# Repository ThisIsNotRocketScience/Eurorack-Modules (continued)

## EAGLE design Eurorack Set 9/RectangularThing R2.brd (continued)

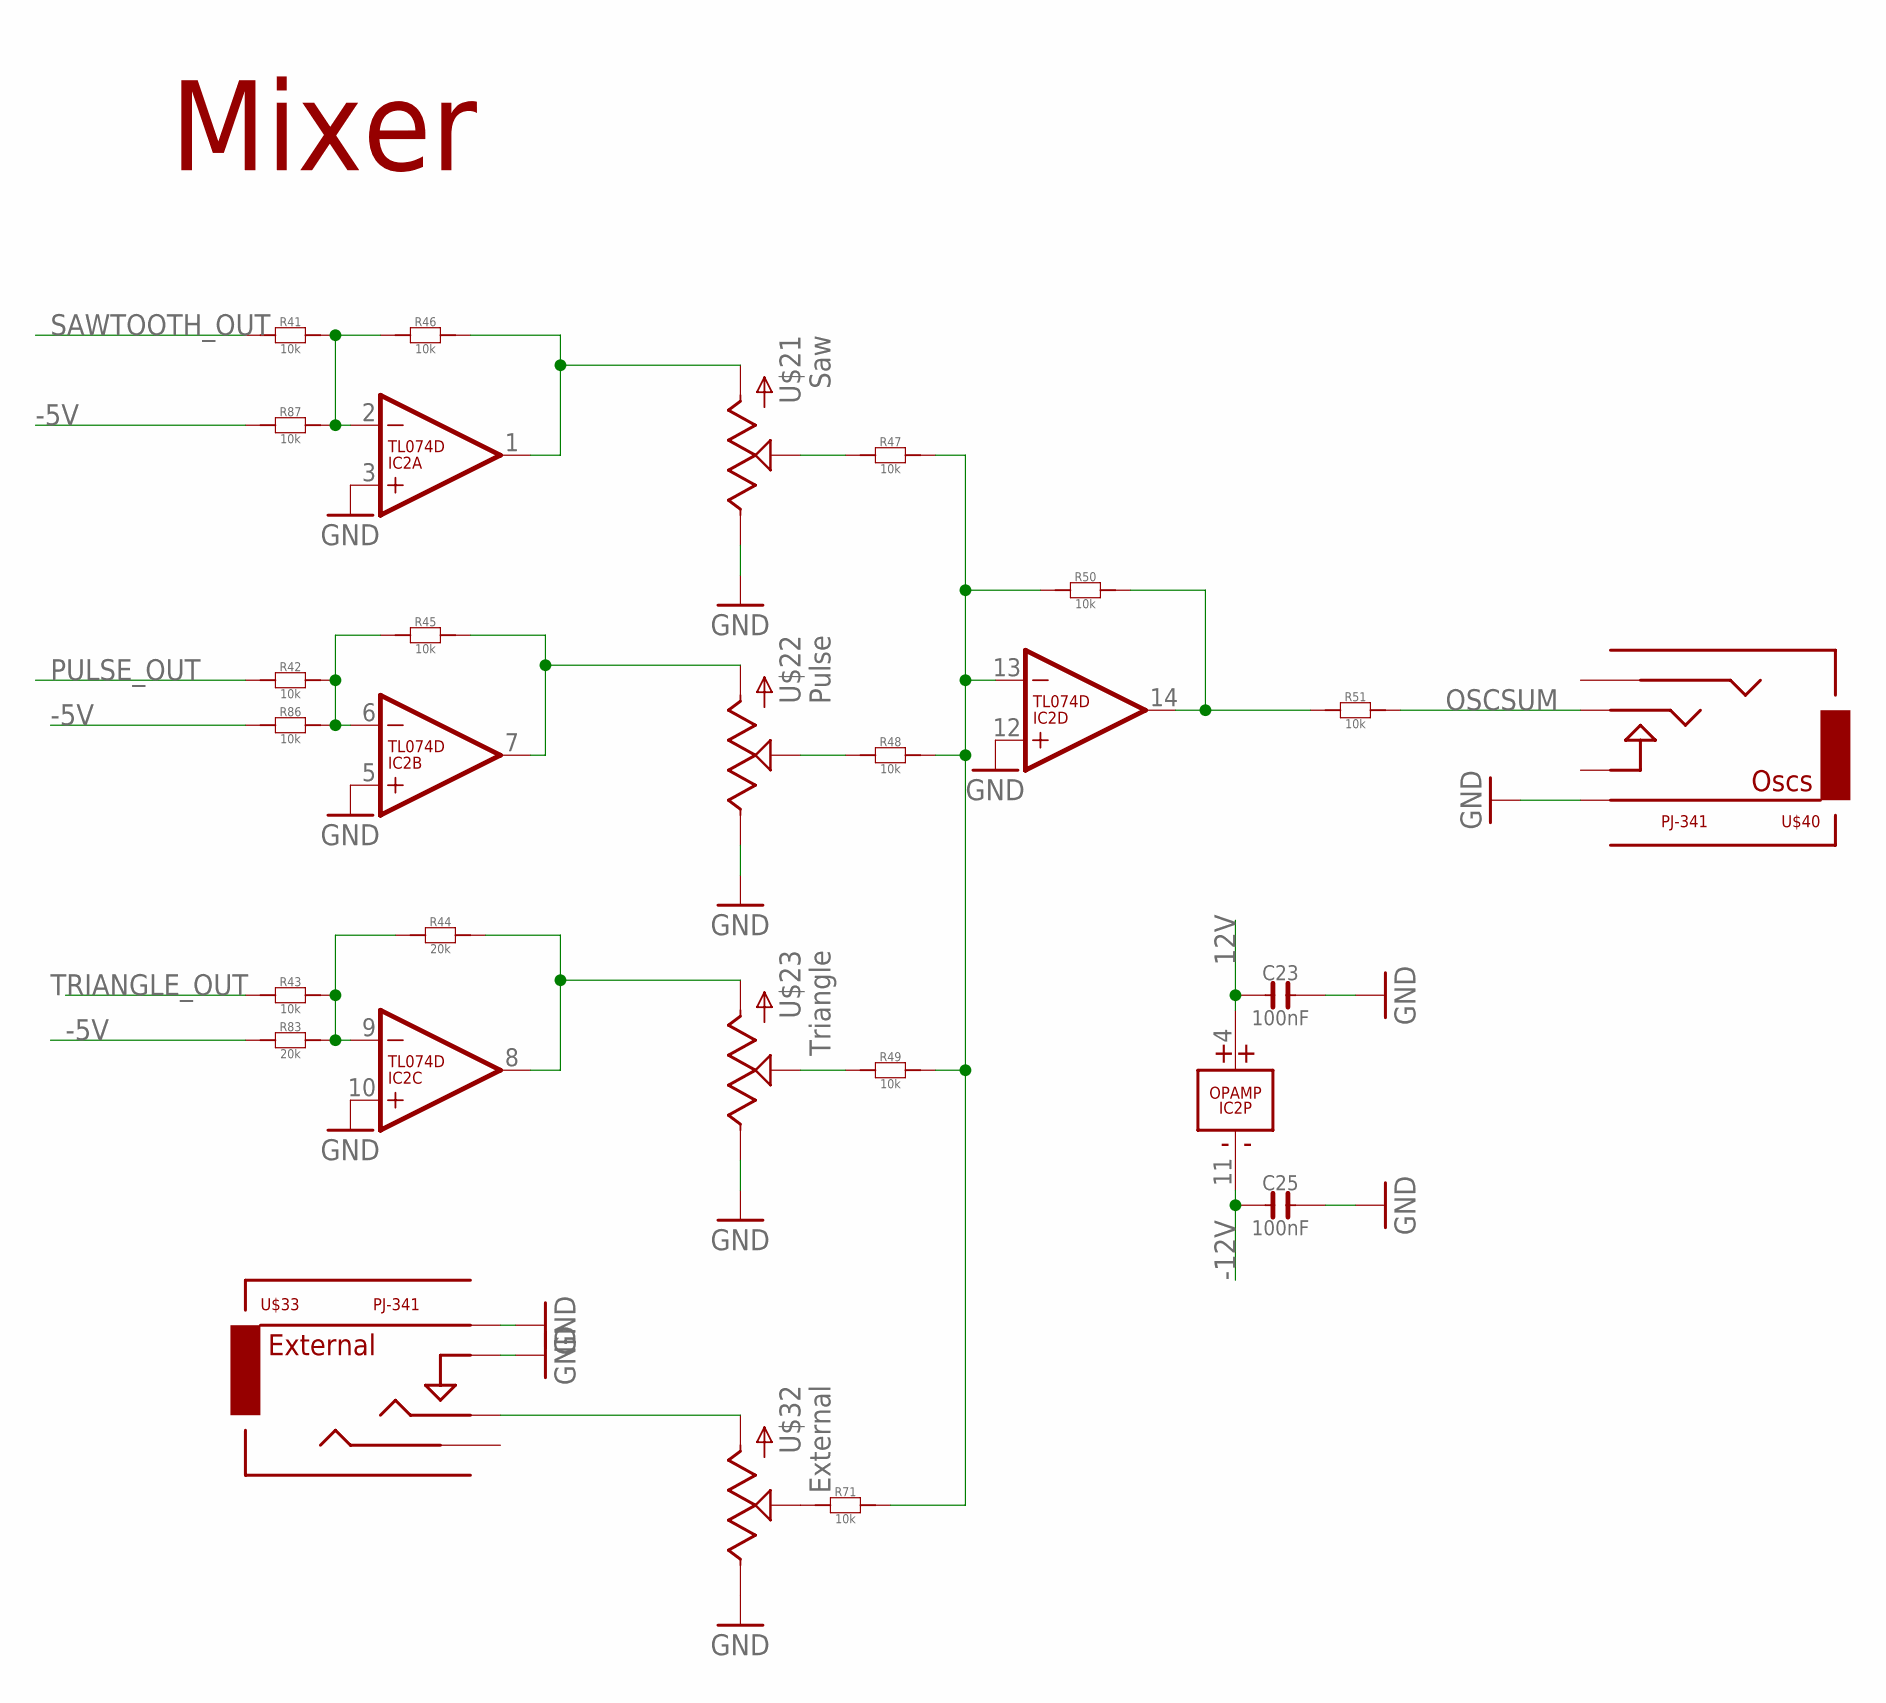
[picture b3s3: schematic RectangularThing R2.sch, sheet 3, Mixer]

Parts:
C23, C25: 100nF; C0603
IC2: TL074D; SO14
R41, R42, R43, R45, R46, R47, R48, R49, R50, R51, R71, R86, R87: 10k; R0603
R44, R83: 20k; R0603
U$21, U$22, U$23, U$32: POTZEPHPOT; OG-POTS_ALPS_POT_VERTICAL
U$33: PJ-341; 3.5MM-JACK-SWITCH-13MM-INPUT
U$40: PJ-341; 3.5MM-JACK-SWITCH-13MM-OUTPUT

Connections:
12V: C23.1, IC2.4 (V+); also elsewhere on the board
-5V: R83.1, R86.1, R87.1; also elsewhere on the board
-12V: C25.1, IC2.11 (V-); also elsewhere on the board
GND: C23.2, C25.2, IC2.3 (+IN), IC2.5 (+IN), IC2.10 (+IN), IC2.12 (+IN), U$21.P$1 (E), U$22.P$1 (E), U$23.P$1 (E), U$32.P$1 (E), U$33.RING@3 (RING), U$33.SWITCH@3 (SWITCH), U$40.RING@3 (RING); also elsewhere on the board
unnamed: IC2.14 (OUT), R50.2, R51.1
unnamed: IC2.13 (-IN), R47.2, R48.2, R49.2, R50.1, R71.2
unnamed: R49.1, U$23.P$2 (S)
unnamed: R48.1, U$22.P$2 (S)
unnamed: R47.1, U$21.P$2 (S)
unnamed: IC2.1 (OUT), R46.2, U$21.P$3 (A)
unnamed: IC2.7 (OUT), R45.2, U$22.P$3 (A)
unnamed: IC2.6 (-IN), R42.2, R45.1, R86.2
unnamed: IC2.2 (-IN), R41.2, R46.1, R87.2
unnamed: IC2.9 (-IN), R43.2, R44.1, R83.2
unnamed: IC2.8 (OUT), R44.2, U$23.P$3 (A)
unnamed: R71.1, U$32.P$2 (S)
unnamed: U$32.P$3 (A), U$33.TIP@3 (TIP)
OSCSUM: R51.2, U$40.TIP@3 (TIP); also elsewhere on the board
PULSE_OUT: R42.1; also elsewhere on the board
SAWTOOTH_OUT: R41.1; also elsewhere on the board
TRIANGLE_OUT: R43.1; also elsewhere on the board

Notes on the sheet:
Mixer

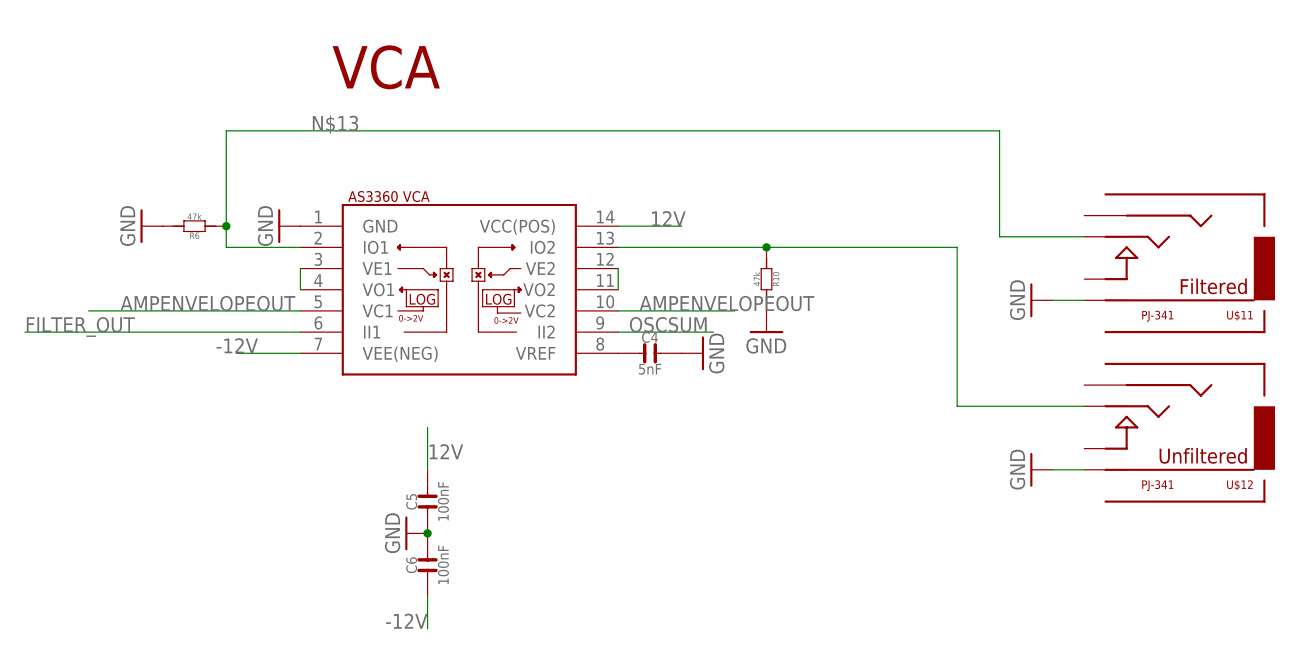
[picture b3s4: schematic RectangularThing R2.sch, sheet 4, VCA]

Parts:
C4: 5nF; C0603
C5, C6: 100nF; C0603
R6, R10: 47k; R0603
U$11, U$12: PJ-341; 3.5MM-JACK-SWITCH-13MM-OUTPUT
U$15: CEM3360; DIL14

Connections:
12V: C5.2, U$15.14 (VCC(POS)); also elsewhere on the board
-12V: C6.1, U$15.7 (VEE(NEG)); also elsewhere on the board
AMPENVELOPEOUT: U$15.5 (VC1), U$15.10 (VC2); also elsewhere on the board
FILTER_OUT: U$15.6 (II1); also elsewhere on the board
GND: C4.2, C5.1, C6.2, R6.2, R10.2, U$11.RING@3 (RING), U$12.RING@3 (RING), U$15.1 (GND); also elsewhere on the board
unnamed: C4.1, U$15.8 (VREF)
unnamed: U$15.3 (VE1), U$15.4 (VO1)
unnamed: R6.1, U$11.TIP@3 (TIP), U$15.2 (IO1)
unnamed: R10.1, U$12.TIP@3 (TIP), U$15.13 (IO2)
unnamed: U$15.11 (VO2), U$15.12 (VE2)
OSCSUM: U$15.9 (II2); also elsewhere on the board

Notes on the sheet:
VCA

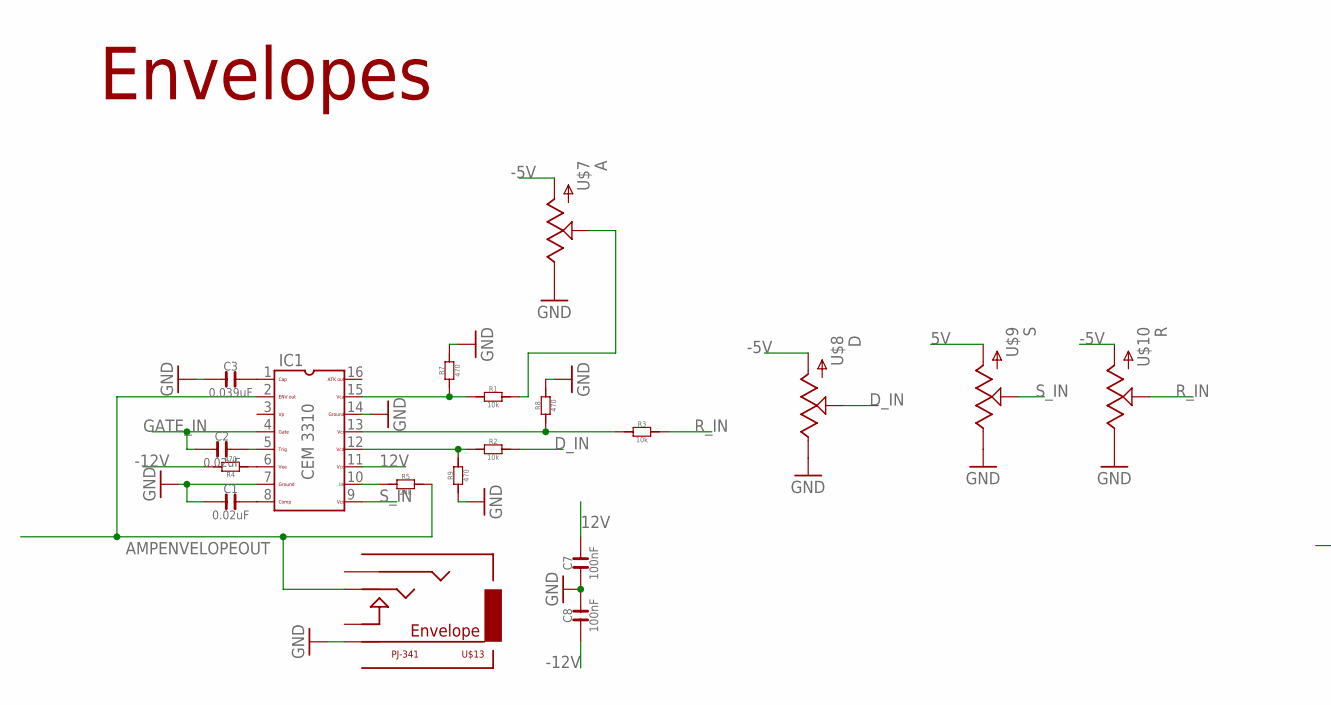
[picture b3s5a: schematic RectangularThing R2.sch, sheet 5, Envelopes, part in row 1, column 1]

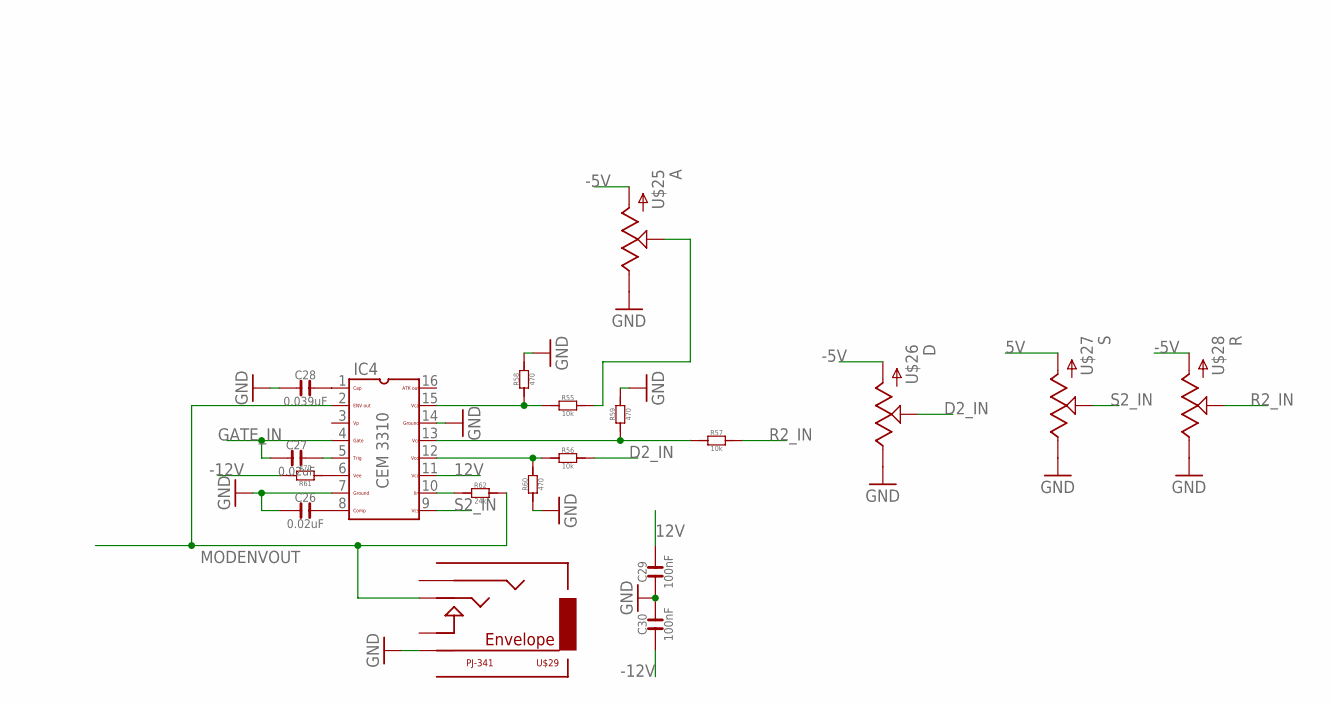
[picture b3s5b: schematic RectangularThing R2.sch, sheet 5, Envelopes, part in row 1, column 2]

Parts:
C1, C2, C26, C27: 0.02uF; C0603
C3, C28: 0.039uF; C0603
C7, C8, C29, C30: 100nF; C0603
IC1, IC4: CEM3310; DIL16
R1, R2, R3, R55, R56, R57: 10k; R0603
R4, R7, R8, R9, R58, R59, R60, R61: 470; R0603
R5, R62: 24k; R0603
U$7, U$8, U$9, U$10, U$25, U$26, U$27, U$28: POTZEPHPOT; OG-POTS_ALPS_POT_VERTICAL
U$13, U$29: PJ-341; 3.5MM-JACK-SWITCH-13MM-OUTPUT

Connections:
5V: U$9.P$3 (A), U$27.P$3 (A); also elsewhere on the board
12V: C7.2, C29.2, IC1.11, IC4.11; also elsewhere on the board
-5V: U$7.P$3 (A), U$8.P$3 (A), U$10.P$3 (A), U$25.P$3 (A), U$26.P$3 (A), U$28.P$3 (A); also elsewhere on the board
-12V: C8.1, C30.1, R4.2, R61.2; also elsewhere on the board
A2_IN: R55.2, U$25.P$2 (S)
AMPENVELOPEOUT: IC1.2, R5.2, U$13.TIP@3 (TIP); also elsewhere on the board
A_IN: R1.2, U$7.P$2 (S)
D2_IN: R56.2, U$26.P$2 (S)
D_IN: R2.2, U$8.P$2 (S)
GATE_IN: C2.1, C27.1, IC1.4, IC4.4; also elsewhere on the board
GND: C1.1, C3.1, C7.1, C8.2, C26.1, C28.1, C29.1, C30.2, IC1.7, IC1.14, IC4.7, IC4.14, R7.2, R8.2, R9.1, R58.2, R59.2, R60.1, U$7.P$1 (E), U$8.P$1 (E), U$9.P$1 (E), U$10.P$1 (E), U$13.RING@3 (RING), U$25.P$1 (E), U$26.P$1 (E), U$27.P$1 (E), U$28.P$1 (E), U$29.RING@3 (RING); also elsewhere on the board
MODENVOUT: IC4.2, R62.2, U$29.TIP@3 (TIP); also elsewhere on the board
unnamed: IC1.15, R1.1, R7.1
unnamed: IC1.12, R2.1, R9.2
unnamed: IC1.13, R3.1, R8.1
unnamed: C3.2, IC1.1
unnamed: C2.2, IC1.5
unnamed: IC1.6, R4.1
unnamed: C1.2, IC1.8
unnamed: IC1.10, R5.1
unnamed: IC4.15, R55.1, R58.1
unnamed: IC4.12, R56.1, R60.2
unnamed: IC4.13, R57.1, R59.1
unnamed: C27.2, IC4.5
unnamed: IC4.6, R61.1
unnamed: C26.2, IC4.8
unnamed: IC4.10, R62.1
unnamed: C28.2, IC4.1
R2_IN: R57.2, U$28.P$2 (S)
R_IN: R3.2, U$10.P$2 (S)
S2_IN: IC4.9, U$27.P$2 (S)
S_IN: IC1.9, U$9.P$2 (S)

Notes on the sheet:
Envelopes

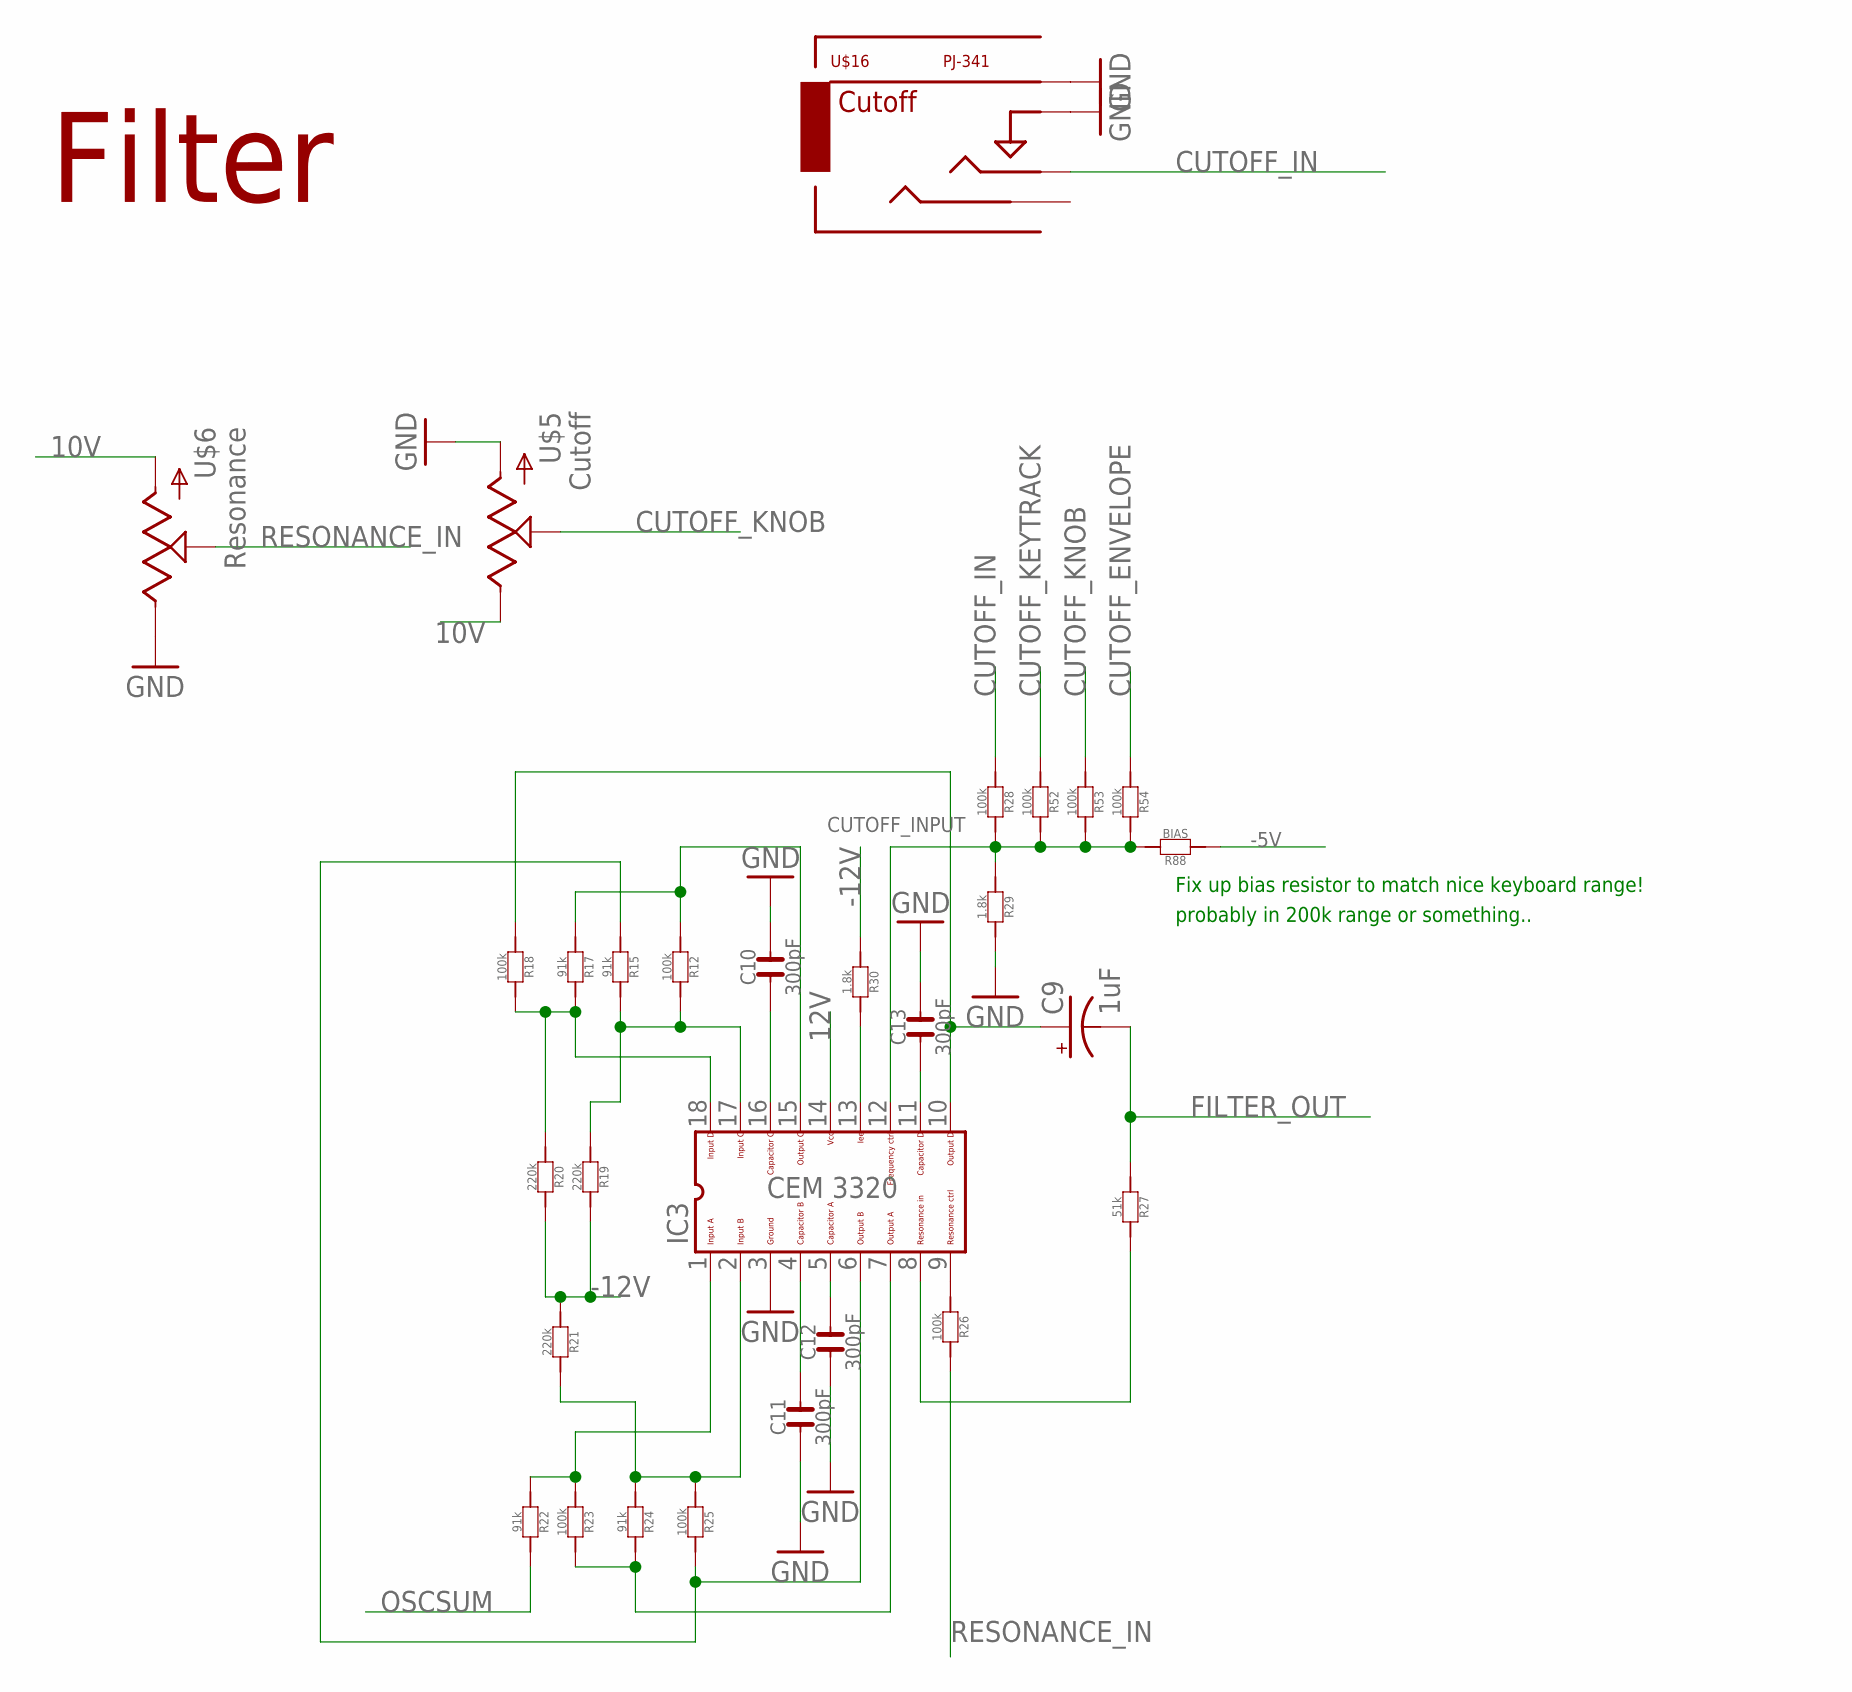
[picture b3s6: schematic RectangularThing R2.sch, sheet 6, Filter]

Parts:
C9: 1uF; 153CLV-0505
C10, C11, C12, C13: 300pF; C0603
IC3: CEM3320; DIL18
R12, R18, R23, R25, R26, R28, R52, R53, R54: 100k; R0603
R15, R17, R22, R24: 91k; R0603
R19, R20, R21: 220k; R0603
R27: 51k; R0603
R29, R30: 1.8k; R0603
R88: BIAS; R0603
U$5, U$6: POTZEPHPOT; OG-POTS_ALPS_POT_VERTICAL
U$16: PJ-341; 3.5MM-JACK-SWITCH-13MM-INPUT

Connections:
10V: U$5.P$1 (E), U$6.P$3 (A); also elsewhere on the board
12V: IC3.14; also elsewhere on the board
-5V: R88.1; also elsewhere on the board
-12V: R19.2, R20.2, R21.1, R30.1; also elsewhere on the board
CUTOFF_ENVELOPE: R54.1; also elsewhere on the board
CUTOFF_IN: R28.1, U$16.TIP@3 (TIP)
CUTOFF_INPUT: IC3.12, R28.2, R29.1, R52.2, R53.2, R54.2, R88.2
CUTOFF_KEYTRACK: R52.1; also elsewhere on the board
CUTOFF_KNOB: R53.1, U$5.P$2 (S)
FILTER_OUT: C9.-, R27.1; also elsewhere on the board
GND: C10.2, C11.1, C12.1, C13.2, IC3.3, R29.2, U$5.P$3 (A), U$6.P$1 (E), U$16.RING@3 (RING), U$16.SWITCH@3 (SWITCH); also elsewhere on the board
unnamed: C10.1, IC3.16
unnamed: C11.2, IC3.4
unnamed: C12.2, IC3.5
unnamed: C13.1, IC3.11
unnamed: IC3.9, R26.1
unnamed: IC3.1, R22.1, R23.1
unnamed: IC3.7, R23.2, R24.2
unnamed: IC3.6, R15.1, R25.2
unnamed: IC3.18, R17.2, R18.2, R20.1
unnamed: IC3.17, R12.2, R15.2, R19.1
unnamed: IC3.15, R12.1, R17.1
unnamed: IC3.13, R30.2
unnamed: C9.+, IC3.10, R18.1
unnamed: IC3.8, R27.2
unnamed: IC3.2, R21.2, R24.1, R25.1
OSCSUM: R22.2; also elsewhere on the board
RESONANCE_IN: R26.2, U$6.P$2 (S)

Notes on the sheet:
Filter
Fix up bias resistor to match nice keyboard range!
probably in 200k range or something..

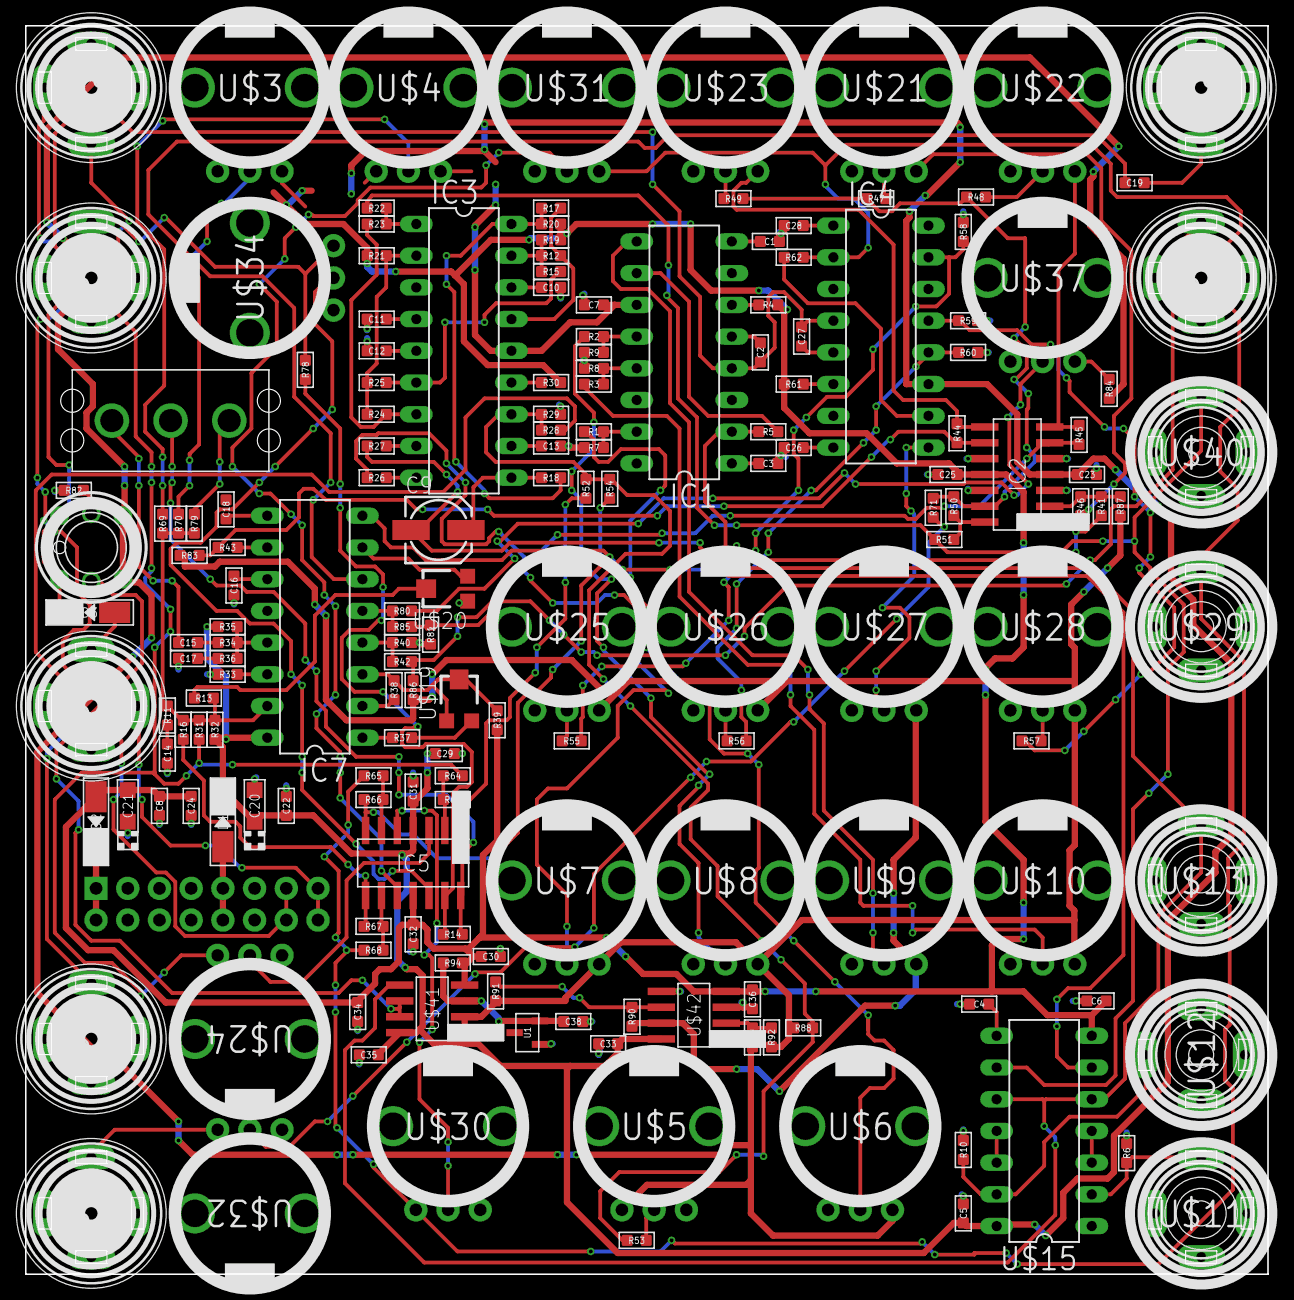
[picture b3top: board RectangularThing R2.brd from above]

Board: 2 copper layers, 99.5 x 100.0 mm, 176 parts (1 on the bottom side), 123 nets.

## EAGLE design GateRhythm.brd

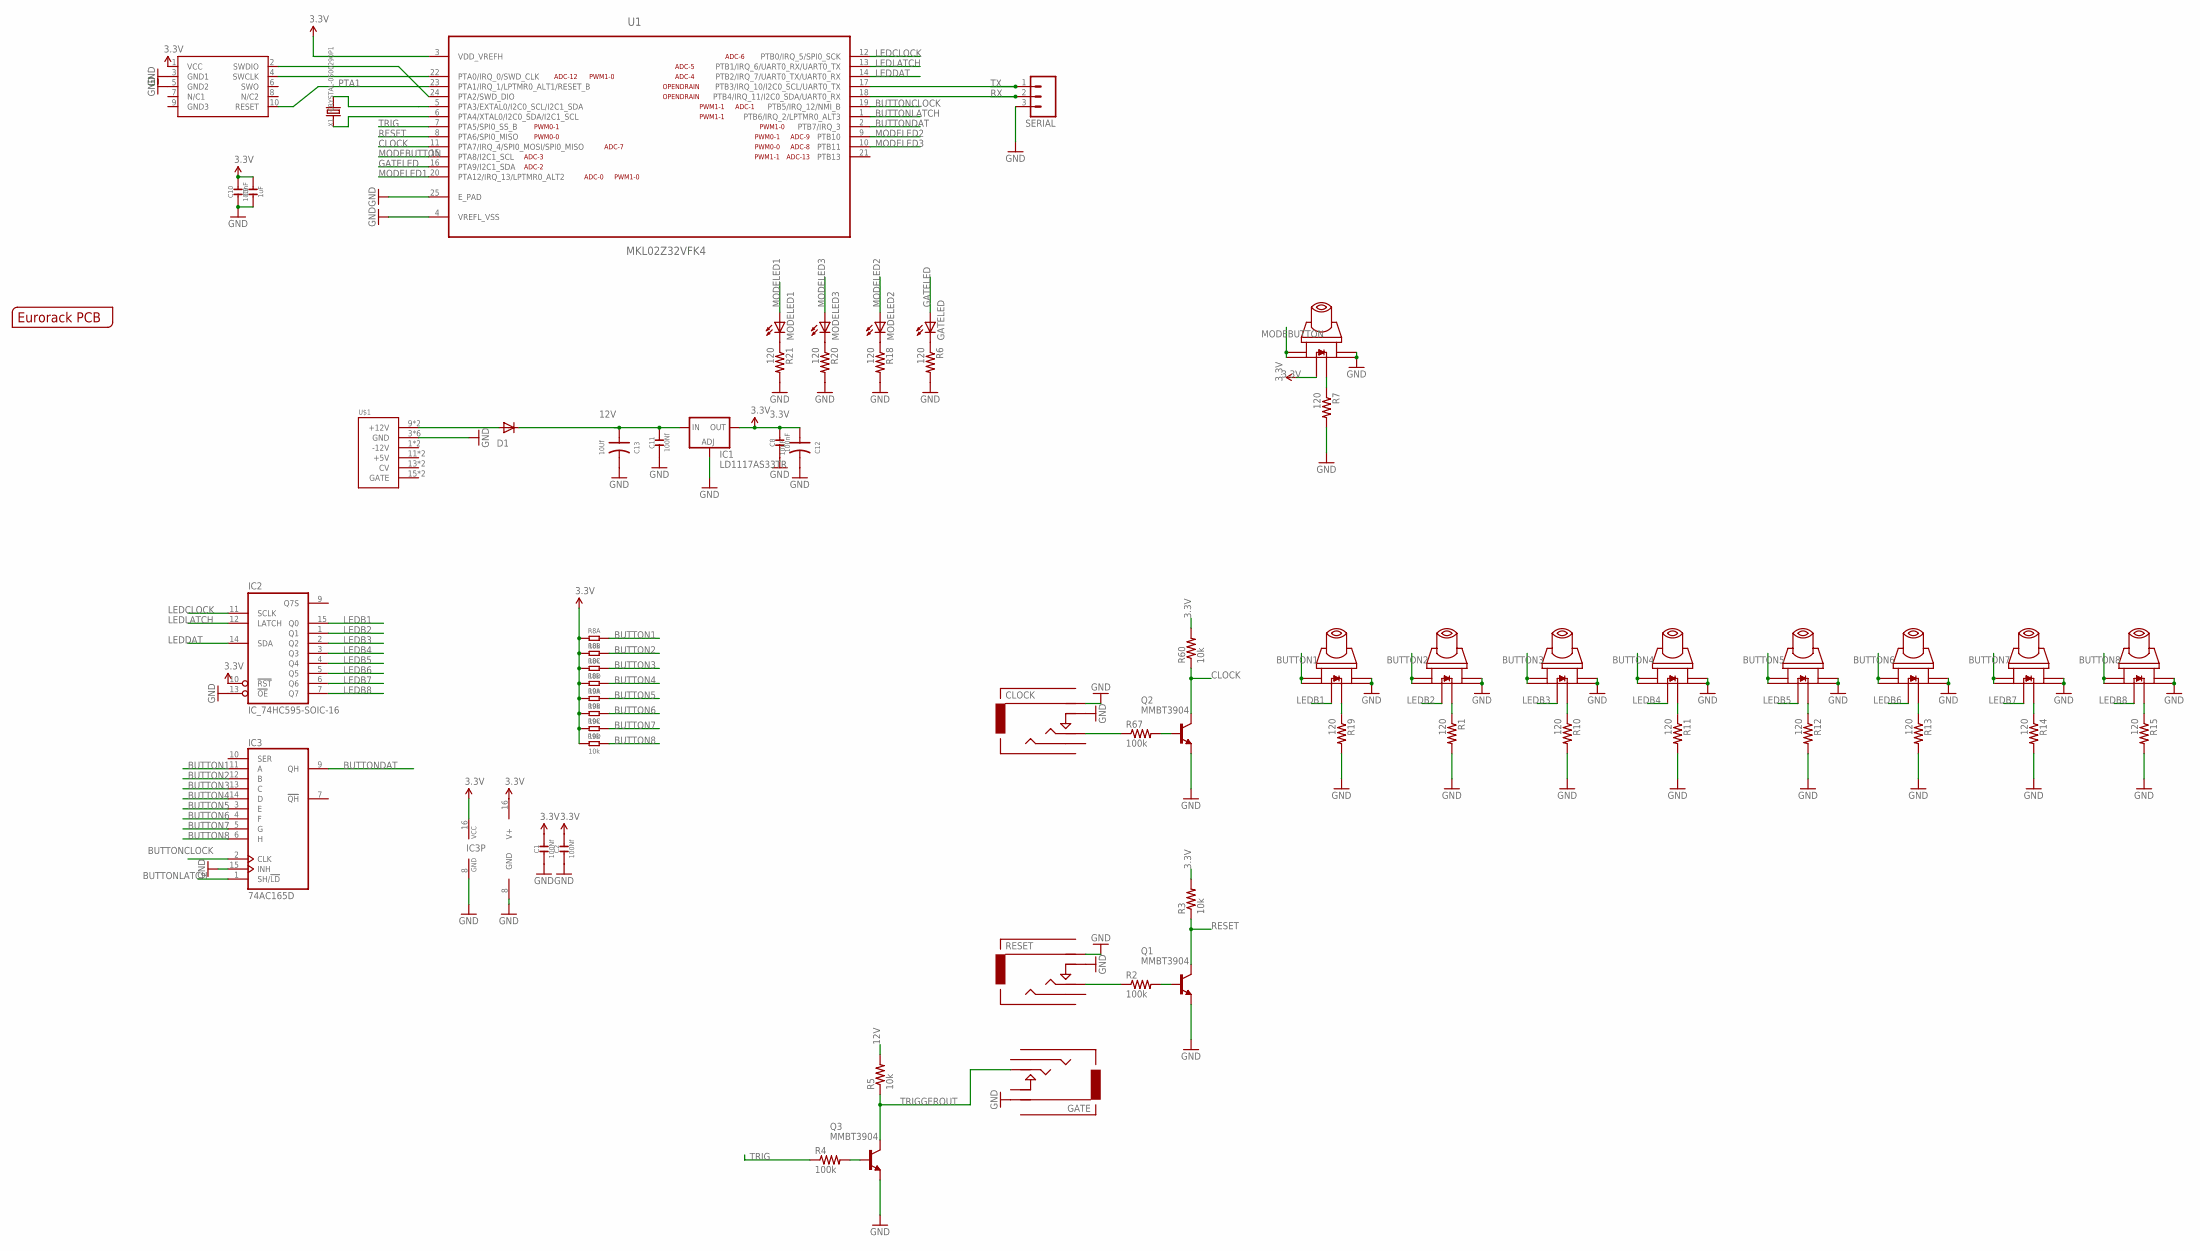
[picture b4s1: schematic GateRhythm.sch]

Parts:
B1, B2, B3, B4, B5, B6, B7, B8, B9: SWITCH_W_LED_PB6149L-X-102WHITE; PB6149L
C1, C2, C11: 100Nf; C0603
C8, C10: 100nF; C0603
C9: 1uF; C0603
C12: 10uF; AVX-A
C13: 10Uf; AVX-A
CLOCK: Clock; 3.5MM-JACK-SWITCH-13MM-INPUT
D1: 1N5819HW; SOD123
GATE: Gate; 3.5MM-JACK-SWITCH-13MM-OUTPUT
GATELED: LED3MM
IC1: LD1117AS33TR; SOT223
IC2: IC_74HC595-SOIC-16; SOIC-16
IC3: 74AC165D; SO16
MODELED1, MODELED2, MODELED3: LED3MM
Q1, Q2, Q3: MMBT3904; SOT23-BEC
R1, R6, R7, R10, R11, R12, R13, R14, R15, R18, R19, R20, R21: 120; R0603
R2, R4, R67: 100k; R0603
R3, R5, R60: 10k; R0603
R8, R9: 10k; R1206-8
RESET: Reset; 3.5MM-JACK-SWITCH-13MM-INPUT
SERIAL: M03PTH; 1X03
SWD1: CORTEX_SWD; M50-3600542
U1: MKL02Z32VFK4; QFN50P400X400X100-25N
U$1: POWER; POWER_16
U$2: EURORACK_PCB6HP; EURORACK6HPPCB
X1: CRYSTAL-0500290P1; 2P-SMD-5.0X3.2

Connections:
3.3V: B9.LEDPOS (POS), C1.2, C2.2, C8.2, C9.2, C10.2, C12.+ (1), IC1.2 (OUT), IC1.4 (OUT), IC2.10 (!RST), IC2.16 (V+), IC3.16 (VCC), R3.2, R8.1, R8.2 (1), R8.3 (1), R8.4 (1), R9.1, R9.2 (1), R9.3 (1), R9.4 (1), R60.2, SWD1.1 (VCC), U1.3 (VDD_VREFH)
12V: C11.2, C13.+ (1), D1.C, IC1.3 (IN), R5.2
BUTTON1: B1.1, B1.2, IC3.11 (A), R8.8 (2)
BUTTON2: B2.1, B2.2, IC3.12 (B), R8.7 (2)
BUTTON3: B3.1, B3.2, IC3.13 (C), R8.6 (2)
BUTTON4: B4.1, B4.2, IC3.14 (D), R8.5 (2)
BUTTON5: B5.1, B5.2, IC3.3 (E), R9.8 (2)
BUTTON6: B6.1, B6.2, IC3.4 (F), R9.7 (2)
BUTTON7: B7.1, B7.2, IC3.5 (G), R9.6 (2)
BUTTON8: B8.1, B8.2, IC3.6 (H), R9.5 (2)
BUTTONCLOCK: IC3.2 (CLK), U1.19 (PTB5/IRQ_12/NMI_B)
BUTTONDAT: IC3.9 (QH), U1.2 (PTB7/IRQ_3)
BUTTONLATCH: IC3.1 (SH/!LD), U1.1 (PTB6/IRQ_2/LPTMR0_ALT3)
CLOCK: Q2.C, R60.1, U1.11 (PTA7/IRQ_4/SPI0_MOSI/SPI0_MISO)
GATELED: GATELED.A, U1.16 (PTA9/I2C1_SDA)
GND: B1.3, B1.4, B2.3, B2.4, B3.3, B3.4, B4.3, B4.4, B5.3, B5.4, B6.3, B6.4, B7.3, B7.4, B8.3, B8.4, B9.3, B9.4, C1.1, C2.1, C8.1, C9.1, C10.1, C11.1, C12.- (2), C13.- (2), CLOCK.RING@1 (RING), CLOCK.RING@2 (RING), CLOCK.SWITCH@1 (SWITCH), CLOCK.SWITCH@2 (SWITCH), GATE.RING@1 (RING), GATE.RING@2 (RING), IC1.1 (ADJ), IC2.8 (GND), IC2.13 (!OE), IC3.8 (GND), IC3.15 (INH), Q1.E, Q2.E, Q3.E, R1.2, R6.2, R7.2, R10.2, R11.2, R12.2, R13.2, R14.2, R15.2, R18.2, R19.2, R20.2, R21.2, RESET.RING@1 (RING), RESET.RING@2 (RING), RESET.SWITCH@1 (SWITCH), RESET.SWITCH@2 (SWITCH), SERIAL.3, SWD1.3 (GND1), SWD1.5 (GND2), U1.4 (VREFL_VSS), U1.25 (E_PAD), U$1.3 (GND), U$1.4 (GND), U$1.5 (GND), U$1.6 (GND), U$1.7 (GND), U$1.8 (GND)
LEDB1: B1.LEDPOS (POS), IC2.15 (Q0)
LEDB2: B2.LEDPOS (POS), IC2.1 (Q1)
LEDB3: B3.LEDPOS (POS), IC2.2 (Q2)
LEDB4: B4.LEDPOS (POS), IC2.3 (Q3)
LEDB5: B5.LEDPOS (POS), IC2.4 (Q4)
LEDB6: B6.LEDPOS (POS), IC2.5 (Q5)
LEDB7: B7.LEDPOS (POS), IC2.6 (Q6)
LEDB8: B8.LEDPOS (POS), IC2.7 (Q7)
LEDCLOCK: IC2.11 (SCLK), U1.12 (PTB0/IRQ_5/SPI0_SCK)
LEDDAT: IC2.14 (SDA), U1.14 (PTB2/IRQ_7/UART0_TX/UART0_RX)
LEDLATCH: IC2.12 (LATCH), U1.13 (PTB1/IRQ_6/UART0_RX/UART0_TX)
MODEBUTTON: B9.1, B9.2, U1.15 (PTA8/I2C1_SCL)
MODELED1: MODELED1.A, U1.20 (PTA12/IRQ_13/LPTMR0_ALT2)
MODELED2: MODELED2.A, U1.9 (PTB10)
MODELED3: MODELED3.A, U1.10 (PTB11)
unnamed: U1.5 (PTA3/EXTAL0/I2C0_SCL/I2C1_SDA), X1.2
unnamed: U1.6 (PTA4/XTAL0/I2C0_SDA/I2C1_SCL), X1.1
unnamed: B2.LEDNEG (NEG), R1.1
unnamed: Q1.B, R2.2
unnamed: SWD1.4 (SWCLK), U1.22 (PTA0/IRQ_0/SWD_CLK)
unnamed: R2.1, RESET.TIP@1 (TIP), RESET.TIP@2 (TIP)
unnamed: SWD1.2 (SWDIO), U1.24 (PTA2/SWD_DIO)
unnamed: B3.LEDNEG (NEG), R10.1
unnamed: Q3.B, R4.2
unnamed: GATELED.K (C), R6.1
unnamed: B9.LEDNEG (NEG), R7.1
unnamed: D1.A, U$1.9 (+12V), U$1.10 (+12V)
unnamed: B1.LEDNEG (NEG), R19.1
unnamed: MODELED2.K (C), R18.1
unnamed: MODELED3.K (C), R20.1
unnamed: MODELED1.K (C), R21.1
unnamed: B4.LEDNEG (NEG), R11.1
unnamed: B5.LEDNEG (NEG), R12.1
unnamed: B6.LEDNEG (NEG), R13.1
unnamed: B7.LEDNEG (NEG), R14.1
unnamed: B8.LEDNEG (NEG), R15.1
unnamed: CLOCK.TIP@1 (TIP), CLOCK.TIP@2 (TIP), R67.1
unnamed: Q2.B, R67.2
PTA1: SWD1.10 (RESET), U1.23 (PTA1/IRQ_1/LPTMR0_ALT1/RESET_B)
RESET: Q1.C, R3.1, U1.8 (PTA6/SPI0_MISO)
RX: SERIAL.2, U1.18 (PTB4/IRQ_11/I2C0_SDA/UART0_RX)
TRIG: R4.1, U1.7 (PTA5/SPI0_SS_B)
TRIGGEROUT: GATE.TIP@1 (TIP), GATE.TIP@2 (TIP), Q3.C, R5.1
TX: SERIAL.1, U1.17 (PTB3/IRQ_10/I2C0_SCL/UART0_TX)

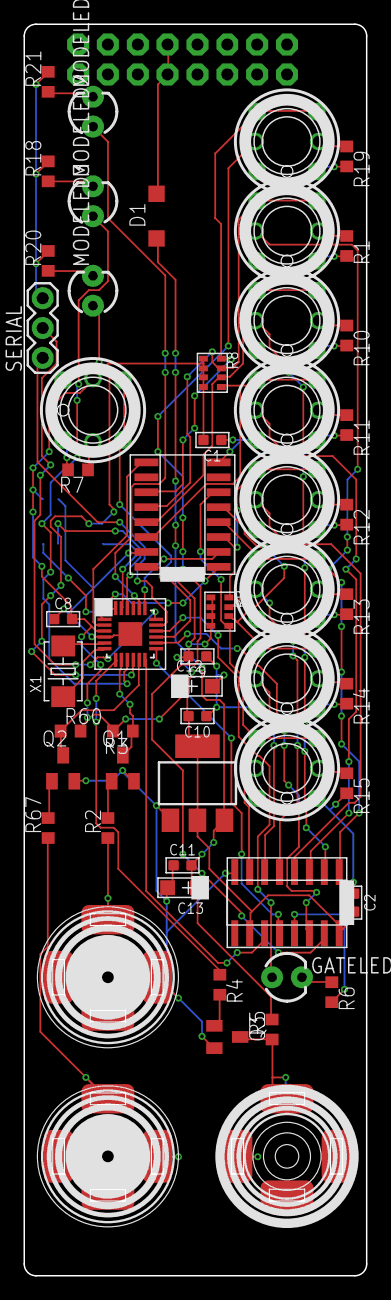
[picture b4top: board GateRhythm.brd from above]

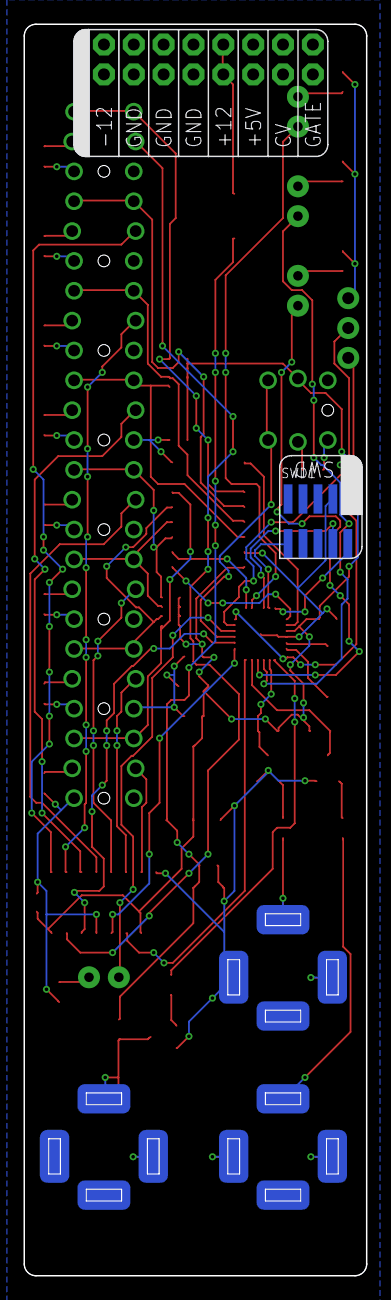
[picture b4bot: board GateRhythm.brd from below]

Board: 2 copper layers, 29.1 x 106.5 mm, 58 parts (2 on the bottom side), 60 nets.
